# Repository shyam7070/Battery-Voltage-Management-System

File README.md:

# Battery-Voltage-Management-System

# Overview
This project is a Battery Voltage Monitoring System designed using an Arduino Uno. It measures the voltage of a 4.2V (2-cell) battery using a voltage divider circuit and displays the real-time voltage on an LCD/OLED screen. The system also features a low battery warning through a buzzer or LED when the voltage drops below 3.8V.

# Features

Real-time Voltage Measurement: Monitors and displays battery voltage continuously.
Voltage Divider Circuit: Safely steps down the battery voltage to a range compatible with the Arduino’s ADC.
Low Battery Alert: Activates a buzzer/LED when voltage falls below 3.8V.
Display Output: Supports 16x2 LCD or OLED display via I2C or parallel interface.
Optional Serial Output: Logs voltage data to the serial monitor for debugging.

# Technical Details
Microcontroller: Arduino Uno
Voltage Measurement Range: Up to 5V (stepped down to 3.3V)

# Components:
Voltage Divider (two resistors)
16x2 LCD or OLED Display
Buzzer/LED for low battery alert
Battery Connector (XT60, DC Jack, or Screw Terminal)
PCB Design: Developed using KiCad with proper routing, ground planes, and component spacing.

# Project Structure
Circuit_Schematic.pdf: Circuit design schematic created in KiCad.
Firmware_Code.ino: Arduino code for reading voltage, displaying it, and triggering low battery alerts.
PCB_Layout: PCB design files including Gerber files for fabrication.

# How to Use
1. Upload the Firmware: Flash the provided Arduino .ino file to your Arduino Uno
2. Assemble the Circuit: Connect all components as per the provided schematic.
3. Power Up: Connect the 4.2V battery to the system.
4. Monitor Voltage: View real-time voltage on the display.
5. Low Battery Alert: Buzzer/LED will activate if the voltage is below 3.8V.

# Tools Used
Arduino IDE: For firmware development.
KiCad: For circuit schematic and PCB design.

# Future Enhancements
Add data logging via serial monitor.
Integrate a charging module (optional).

# Acknowledgments
This project was developed as part of an Embedded Electronics & Hardware Internship Screening Test.

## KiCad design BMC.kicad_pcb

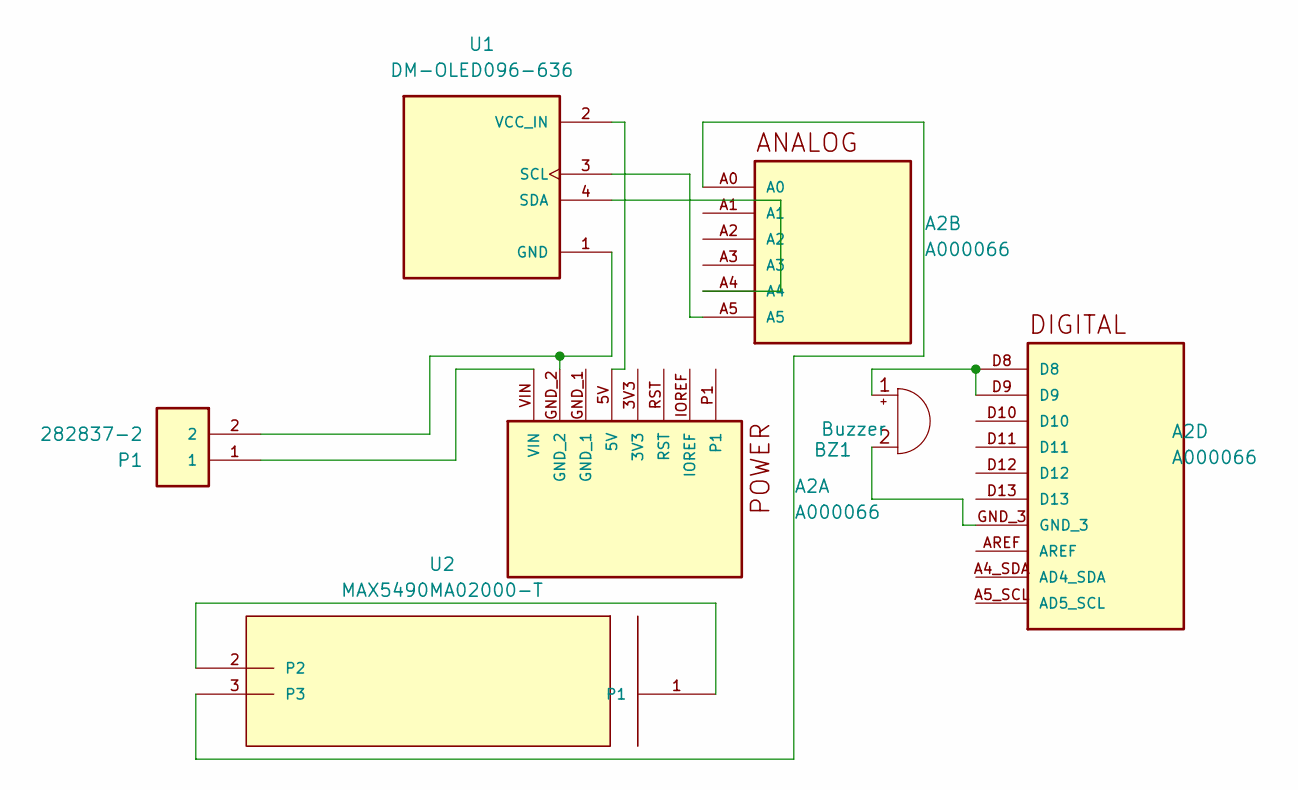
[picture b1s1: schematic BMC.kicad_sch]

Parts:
A2: A000066; ARDUINO_A000066; PARTREV N/A; DigiKey_Part_Number 1050-1024-ND
BZ1: Buzzer; Buzzer_TDK_PS1240P02BT_D12.2mm_H6.5mm
P1: 282837-2; TE_282837-2
U1: DM-OLED096-636; MODULE_DM-OLED096-636
U2: MAX5490MA02000-T; 21-0051H

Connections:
unnamed: A2.VIN, P1.1
unnamed: A2.D8, A2.D9, BZ1.1 (+)
unnamed: A2.GND_3, BZ1.2 (-)
unnamed: A2.GND_2, P1.2, U1.1 (GND)
unnamed: A2.A5, U1.3 (SCL)
unnamed: A2.A4, U1.4 (SDA)
unnamed: A2.5V, U1.2 (VCC_IN)
unnamed: U2.1, U2.2
unnamed: A2.A0, U2.3

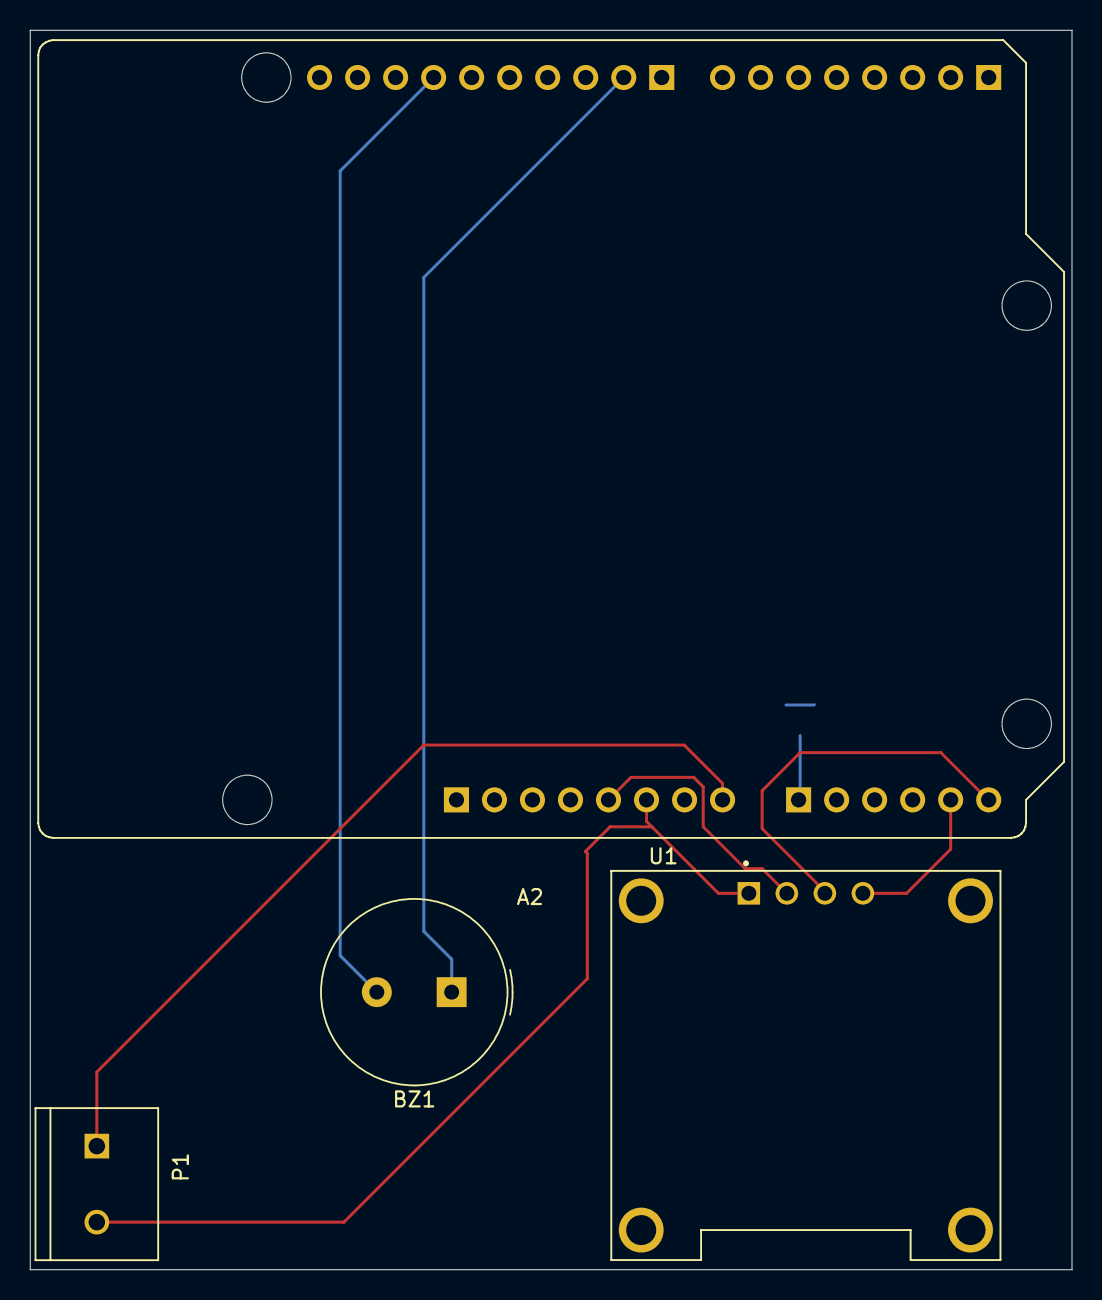
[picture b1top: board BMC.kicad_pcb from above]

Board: 2 copper layers, 69.6 x 82.8 mm, 5 parts (1 on the bottom side), 9 nets.

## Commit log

2025-02-16 README.md
